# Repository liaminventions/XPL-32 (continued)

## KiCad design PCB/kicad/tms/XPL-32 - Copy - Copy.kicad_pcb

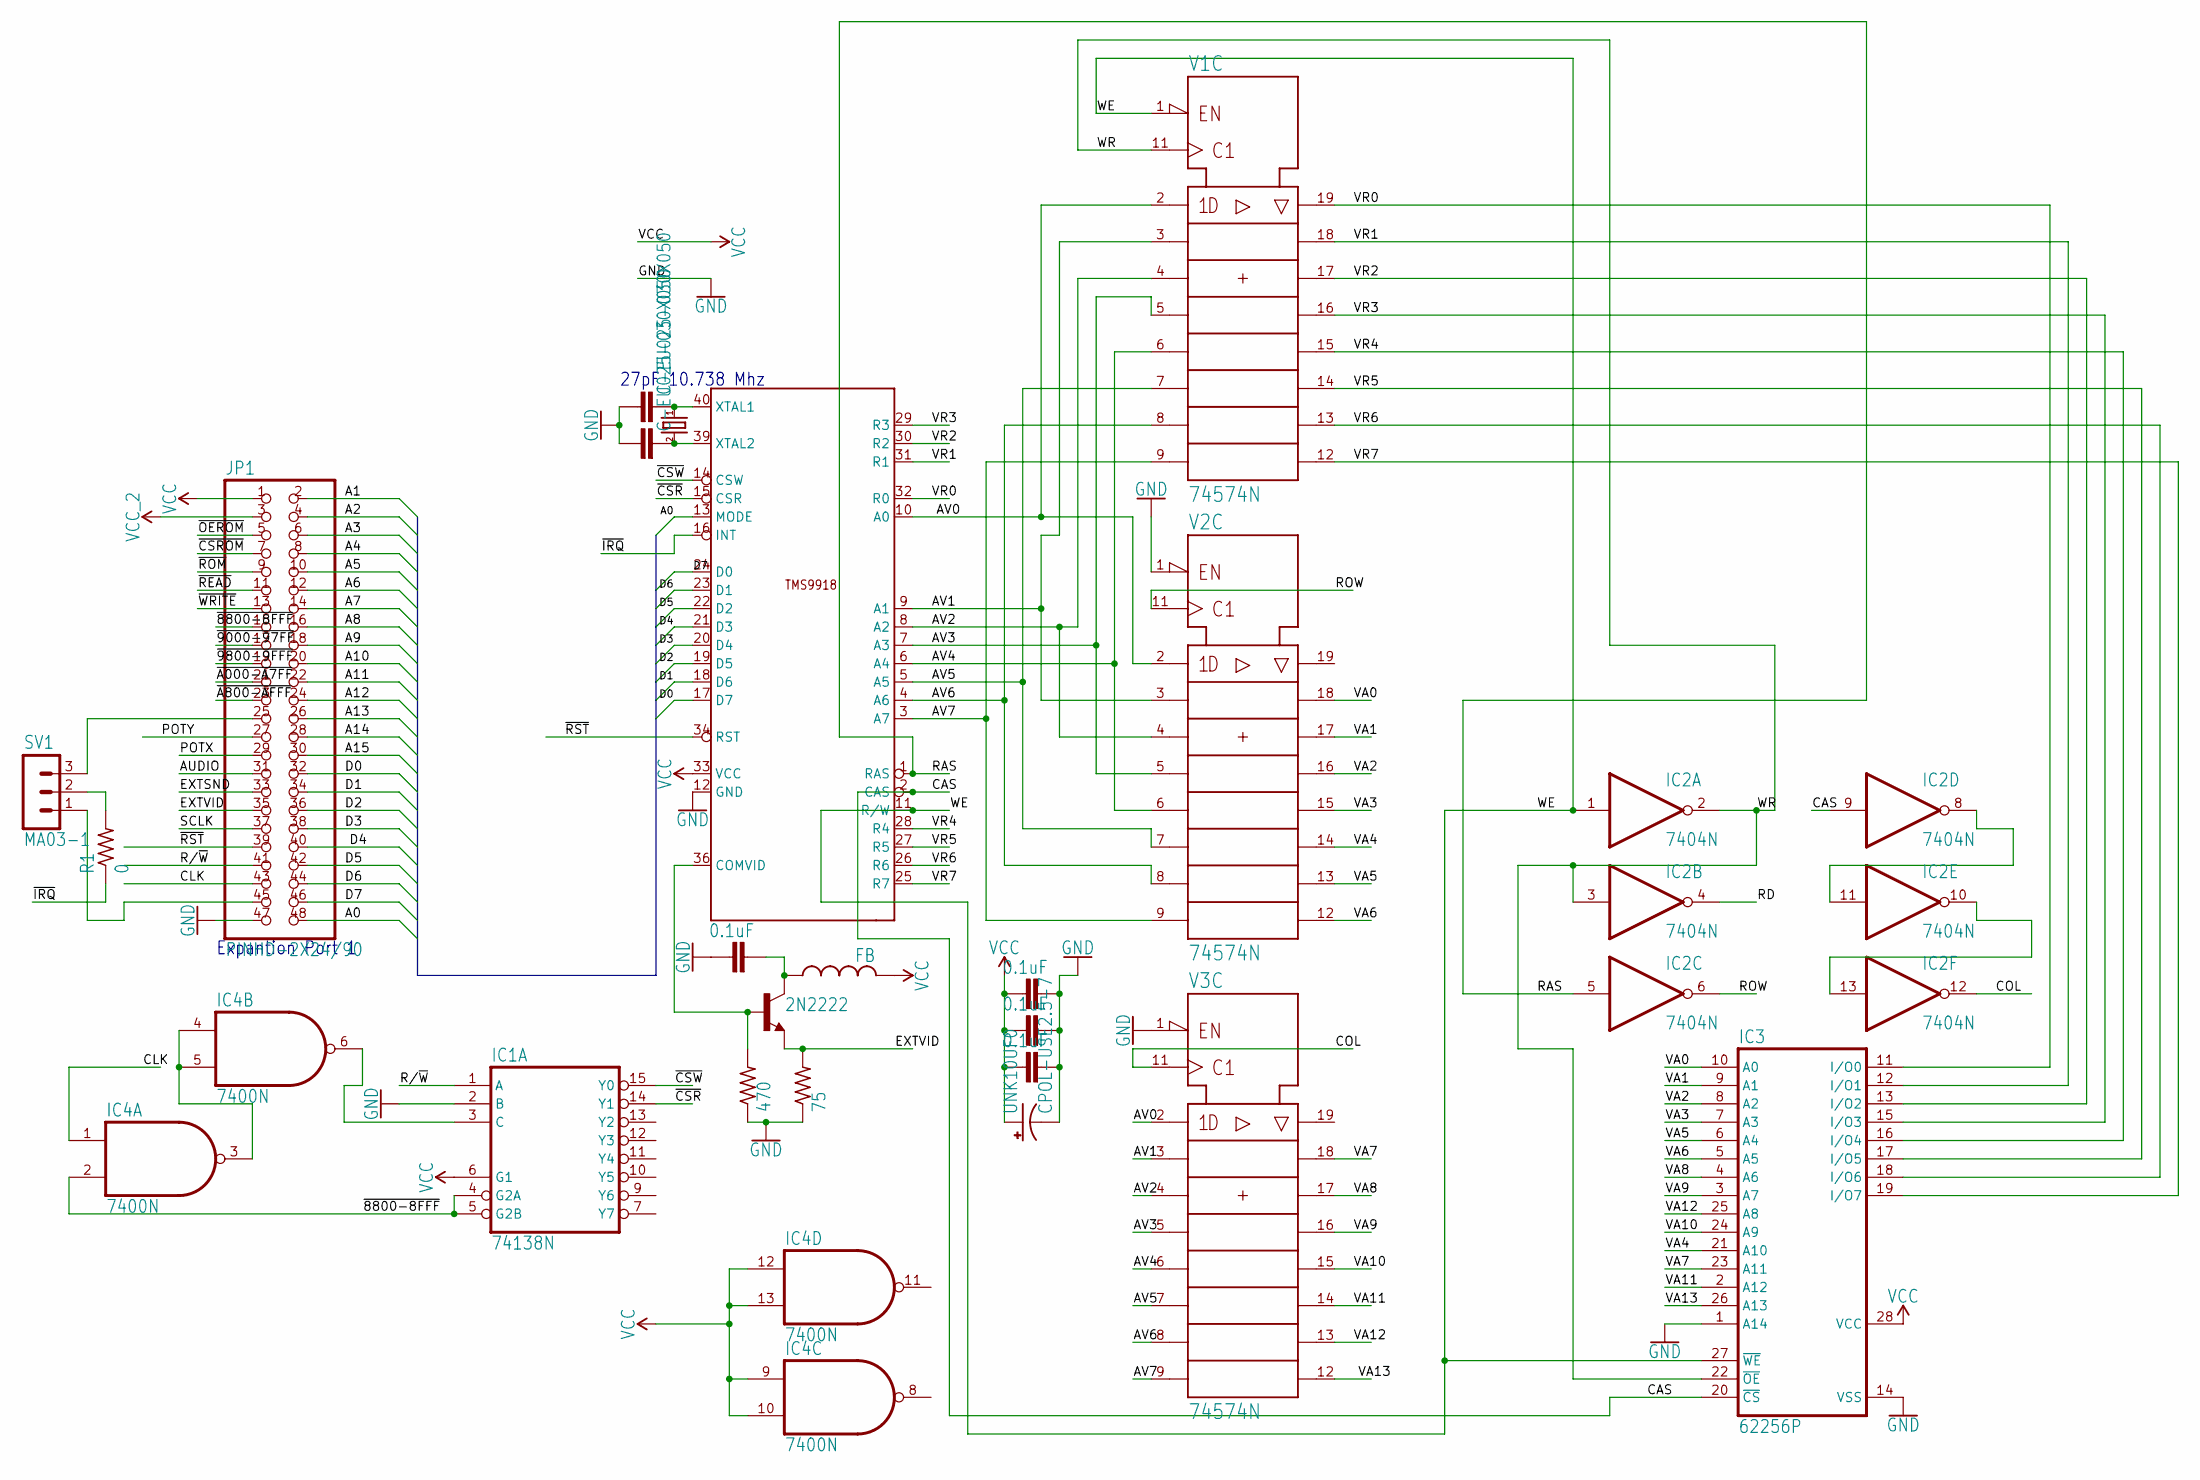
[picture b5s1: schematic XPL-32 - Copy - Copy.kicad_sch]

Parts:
C1, C2, C3, C6: 0.1uF; C025-025X050
IC1: 74138N; DIL16
IC2: 7404N; DIL14
IC3: 62256P; DIL28-6
IC4: 7400N; DIL14
JP1: PINHD-2X24/90; 2X24_90
R1: 0; 0204_7
R9: 470; 0204_7
R10: 75; 0204_7
SV1: MA03-1
T2: 2N2222; TO92-EBC-OVAL
U$4: FB
UNK10.738MHZ0: CRYSTALS-NOGND-HC49; HC49
UNK10UF0: CPOL-USE2.5-7; E2,5-7
UNK30PF0, UNK30PF(2)0: C-EU025-030X050; C025-030X050
V1, V2, V3: 74574N; DIL20
VDP0: TMS9918; DIP-40

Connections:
A0: JP1.48, VDP0.13 (MODE)
A1: JP1.2
A2: JP1.4
A3: JP1.6
A4: JP1.8
A5: JP1.10
A6: JP1.12
A7: JP1.14
A8: JP1.16
A9: JP1.18
A10: JP1.20
A11: JP1.22
A12: JP1.24
A13: JP1.26
A14: JP1.28
A15: JP1.30
AUDIO: JP1.31
AV0: V1.2 (1D), V2.2 (1D), V3.2 (1D), VDP0.10 (A0)
AV1: V1.3 (2D), V2.3 (2D), V3.3 (2D), VDP0.9 (A1)
AV2: V1.4 (3D), V2.4 (3D), V3.4 (3D), VDP0.8 (A2)
AV3: V1.5 (4D), V2.5 (4D), V3.5 (4D), VDP0.7 (A3)
AV4: V1.6 (5D), V2.6 (5D), V3.6 (5D), VDP0.6 (A4)
AV5: V1.7 (6D), V2.7 (6D), V3.7 (6D), VDP0.5 (A5)
AV6: V1.8 (7D), V2.8 (7D), V3.8 (7D), VDP0.4 (A6)
AV7: V1.9 (8D), V2.9 (8D), V3.9 (8D), VDP0.3 (A7)
CAS: IC2.9 (I), IC3.20 (~CS), VDP0.2 (CAS)
CLK: IC4.1 (I0), JP1.43
COL: IC2.12 (O), V3.11 (CLK)
D0: JP1.32, VDP0.17 (D7)
D1: JP1.34, VDP0.18 (D6)
D2: JP1.36, VDP0.19 (D5)
D3: JP1.38, VDP0.20 (D4)
D4: JP1.40, VDP0.21 (D3)
D5: JP1.42, VDP0.22 (D2)
D6: JP1.44, VDP0.23 (D1)
D7: JP1.46, VDP0.24 (D0)
EXTSND: JP1.33
EXTVID: JP1.35, R10.2, T2.E
GND: C1.2, C2.2, C3.2, C6.1, IC1.2 (B), IC1.8 (GND), IC2.7 (GND), IC3.1 (A14), IC3.14 (VSS), IC4.7 (GND), JP1.47, R9.1, R10.1, UNK10UF0.-, UNK30PF0.1, UNK30PF(2)0.1, V1.10 (-UB), V2.1 (~OC), V2.10 (-UB), V3.1 (~OC), V3.10 (-UB), VDP0.12 (GND)
unnamed: IC1.3 (C), IC4.6 (O)
unnamed: JP1.45, SV1.1
unnamed: IC2.8 (O), IC2.11 (I)
unnamed: IC2.10 (O), IC2.13 (I)
unnamed: JP1.25, SV1.3
unnamed: R1.2, SV1.2
unnamed: IC4.3 (O), IC4.4 (I0), IC4.5 (I1)
unnamed: C6.2, T2.C, U$4.P$1 (1)
unnamed: R9.2, T2.B, VDP0.36 (COMVID)
unnamed: UNK10.738MHZ0.1, UNK30PF0.2, VDP0.40 (XTAL1)
unnamed: UNK10.738MHZ0.2, UNK30PF(2)0.2, VDP0.39 (XTAL2)
POTX: JP1.29
POTY: JP1.27
R/~W: IC1.1 (A), JP1.41
RAS: IC2.5 (I), VDP0.1 (RAS)
RD: IC2.4 (O)
ROW: IC2.6 (O), V2.11 (CLK)
SCLK: JP1.37
VA0: IC3.10 (A0), V2.18 (2Q)
VA1: IC3.9 (A1), V2.17 (3Q)
VA2: IC3.8 (A2), V2.16 (4Q)
VA3: IC3.7 (A3), V2.15 (5Q)
VA4: IC3.21 (A10), V2.14 (6Q)
VA5: IC3.6 (A4), V2.13 (7Q)
VA6: IC3.5 (A5), V2.12 (8Q)
VA7: IC3.23 (A11), V3.18 (2Q)
VA8: IC3.4 (A6), V3.17 (3Q)
VA9: IC3.3 (A7), V3.16 (4Q)
VA10: IC3.24 (A9), V3.15 (5Q)
VA11: IC3.2 (A12), V3.14 (6Q)
VA12: IC3.25 (A8), V3.13 (7Q)
VA13: IC3.26 (A13), V3.12 (8Q)
VCC: C1.1, C2.1, C3.1, IC1.6 (G1), IC1.16 (VCC), IC2.14 (VCC), IC3.28 (VCC), IC4.9 (I0), IC4.10 (I1), IC4.12 (I0), IC4.13 (I1), IC4.14 (VCC), JP1.1, U$4.P$2 (2), UNK10UF0.+, V1.20 (+UB), V2.20 (+UB), V3.20 (+UB), VDP0.33 (VCC)
VCC_2: JP1.3
VR0: IC3.11 (I/O0), V1.19 (1Q), VDP0.32 (R0)
VR1: IC3.12 (I/O1), V1.18 (2Q), VDP0.31 (R1)
VR2: IC3.13 (I/O2), V1.17 (3Q), VDP0.30 (R2)
VR3: IC3.15 (I/O3), V1.16 (4Q), VDP0.29 (R3)
VR4: IC3.16 (I/O4), V1.15 (5Q), VDP0.28 (R4)
VR5: IC3.17 (I/O5), V1.14 (6Q), VDP0.27 (R5)
VR6: IC3.18 (I/O6), V1.13 (7Q), VDP0.26 (R6)
VR7: IC3.19 (I/O7), V1.12 (8Q), VDP0.25 (R7)
WE: IC2.1 (I), IC3.27 (~WE), V1.1 (~OC), VDP0.11 (R/W)
WR: IC2.2 (O), IC2.3 (I), IC3.22 (~OE), V1.11 (CLK)
~8800-8FFF: IC1.4 (G2A), IC1.5 (G2B), IC4.2 (I1), JP1.15
~9000-97FF: JP1.17
~9800-9FFF: JP1.19
~A000-A7FF: JP1.21
~A800-AFFF: JP1.23
~CSROM: JP1.7
~CSR: IC1.14 (Y1), VDP0.15 (CSR)
~CSW: IC1.15 (Y0), VDP0.14 (CSW)
~IRQ: R1.1, VDP0.16 (INT)
~OEROM: JP1.5
~READ: JP1.11
~ROM: JP1.9
~RST: JP1.39, VDP0.34 (RST)
~WRITE: JP1.13

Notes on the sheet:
27pF 10.738 Mhz
Expantion Port 1

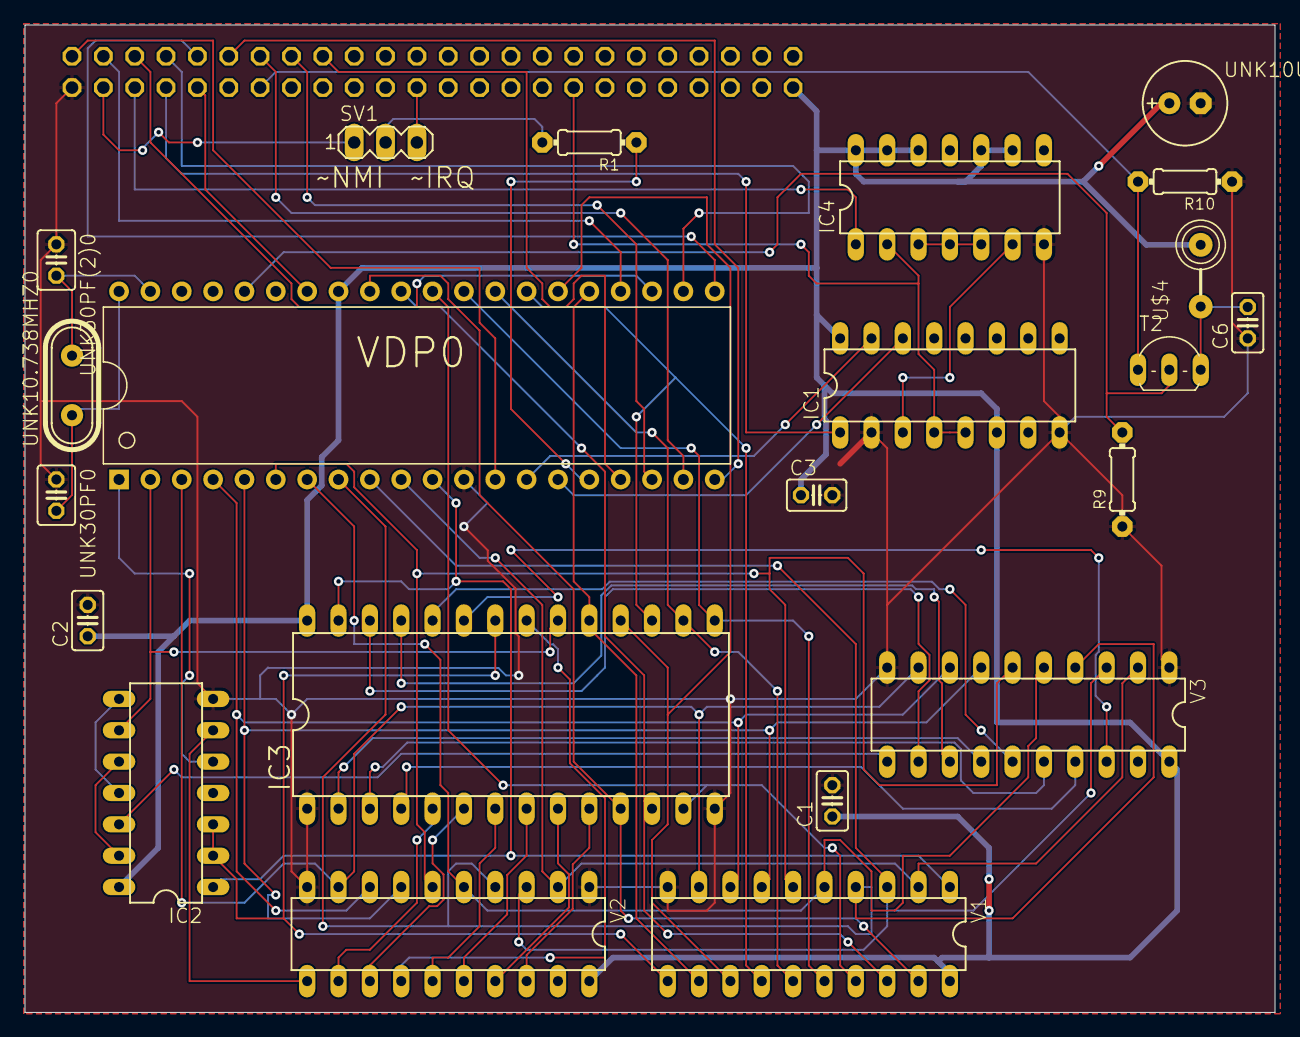
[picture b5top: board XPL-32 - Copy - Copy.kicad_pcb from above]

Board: 2 copper layers, 101.3 x 80.0 mm, 23 parts (1 on the bottom side), 66 nets.

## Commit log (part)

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2023-01-01 have i fixed shortconvert?
2023-01-01 refactor
2023-01-01 maybe its not this?
2023-01-01 oqwe
2023-01-01 With this debug info, i see the issue
2023-01-01 Complete Refactor of the shortconvert system.
2023-01-01 You will work now.
2023-01-01 oh there it is! hehe
2023-01-01 all done!
2023-01-12 clean
2023-01-12 erjieqw
2023-01-12 i dont have time for this
2023-01-20 organise
2023-01-21 add clear command
2023-01-21 fix typos
2023-01-21 add slashpaths?
2023-01-21 fix addr
2023-01-21 wase of time AUUGH
2023-01-23 kernal
2023-01-24 add goofy ahh vim thingy
    aUUUGHHHHH
2023-01-24 update vi
2023-01-24 eqhruewh
2023-01-24 assemble
2023-01-24 iuir
2023-01-24 bugfix
2023-01-24 asmbler da
2023-01-24 Yes.
2023-01-27 update kernal + rearrange + fix memory overlap
2023-01-27 assemble it all together
2023-01-27 update ROM
2023-01-27 werwe
2023-01-31 ok! lets see what arrow keys are
2023-01-31 ccursor test
2023-01-31 generic commit - pay no mind
2023-02-05 add fast mode?
2023-02-05 sizing fix
2023-02-05 quik fixx
2023-02-05 add artifacts
2023-02-05 size
2023-02-05 fix tape kernal defs
2023-02-09 swap
2023-02-21 do not assemble savetest rn
    full re-write of saving
2023-02-21 he he he haw...
    this fixes lots of things...
2023-02-21 noice!
    do not use fat32 in vasm6502 yet
2023-02-21 oh yeah. this is great!
    lots of improvement, but its untested for now
2023-02-21 fix..?
2023-02-22 LETS GO !!
    i think it's done!!!!!!!
    now to test
2023-02-22 test prep (soon)
2023-02-22 testing now
2023-02-22 fix?
2023-02-22 hoho, i got u
2023-02-22 never gonna give you up
2023-02-22 Be fixed now.
2023-02-22 You are done.
2023-02-22 Fired.
2023-02-22 auugh
2023-02-22 gonna try again tomorrow
2023-02-22 oh
    dtrsynhrth
2023-02-22 ho ho ho!
    it works, but its only half a block
2023-02-22 perfect. sd_writesector works
2023-02-22 debuggin time
2023-02-23 many things :100:
    fixin gliches/debug and fix dumb mistakez (lol)
2023-02-23 remove bloat :alien:
2023-02-23 re-arrange and fix savetest i think
2023-02-23 Looking good...
    can't test it now because I didn't bring the XPL with me (on a trip)
2023-02-23 add issue
    overlooked...
2023-02-23 fix EOC handling in fat32_writesector
2023-02-23 workflow: check if cc65 works in a container
2023-02-23 cleanup
2023-02-25 almost there !! (debuggin)
    auugh i mixed up fat32_writenextsector with sd_writesector. probally somewhere else too, hold on...
2023-02-25 ze big e
2023-02-25 oh im dum
    write! not read!
2023-02-25 argh
2023-02-25 Got You.
    "sky sunday" by sinny
2023-02-25 test without
2023-02-25 OMG IT WOKS!
2023-02-25 almost done fixing filesizes
2023-02-25 update bug count
2023-02-25 this is it...
2023-02-25 test
2023-02-25 wow is that what it is?
2023-02-25 ITS DONE!
    oh my...
2023-02-25 IT WORKS! lets try dumping the ROM...
2023-02-25 stability fix?
2023-02-25 AUGH
2023-02-25 FIXED!
    it works!!!!!!!!!!!!!!!!!!!!!!!!!!!!!!!!!!!!!!!!1
2023-02-25 YES! (delete bloat)
2023-02-26 add delete file and set ROM to 16k
2023-02-26 fix
    arrgh inefficient write amount...
2023-02-26 oh i was just dum
2023-02-26 fix aaaaa
    AUUGH !!
2023-02-26 ohhhhhhh
    ic...
2023-02-26 and that
2023-02-26 YAY! RM WORKS!
2023-02-26 add new fat32/sd features to the monitor
2023-02-26 fix assemble
2023-02-26 compile
2023-02-26 :100: EPIC CODER MOMENT !!
2023-02-26 add sd save to the dispatch table
2023-02-26 OMG IT WORKED!
    save command in the monitor! oh wow...
2023-02-26 add file overwriting
2023-02-26 rm that for FAT stability...
2023-02-26 ohhhh
2023-02-26 Be Fixed.
2023-02-26 ohyeah, now RM
2023-02-26 here
2023-02-26 YEAH! RM AND SAVE WORKS!
2023-02-26 check
2023-02-26 All done for today... that was amazing!
2023-02-26 add executable reconition
2023-02-26 KERNAL: update part 1
2023-02-27 finalize kernal def
    done
2023-02-27 add mv and also maybe fix rm? also cleanup
    gotta assemble this on my raspberry pi - hold on...
2023-02-27 whoops - also i gotta add the new fat routines
2023-02-27 ok now i can test
2023-02-27 one moment
2023-02-27 ffind out
2023-02-27 ohhhh is that it?
2023-02-27 fix merge issue
2023-02-27 rguyiwq
2023-02-27 wakeuhyufgef
2023-02-27 Work.
2023-02-27 auugh!!
2023-02-27 oh.
    AUUGH THATS ALL IT IS??!
2023-02-27 -
    -
2023-02-27 Get out, Bug. You are ruining my life.
2023-03-05 redo some things
2023-03-05 quick fix
2023-03-05 ho ho ho!
2023-03-05 fix root name
2023-03-05 why does it display the matrix on startup..?
2023-03-05 fix root symbol
2023-03-05 ehgr
2023-03-06 lesgo
2023-03-06 add dmf
2023-03-06 new image
2023-03-16 fix no directory being showed after root symbol
2023-03-17 iaehh
2023-03-17 changes to asm.sh and rename tms_groove
2023-03-17 oh. (reorginise)
2023-03-17 copy wavrud.s to pong.s (DO NOT USE YET!)
2023-03-18 pong.s better
2023-03-18 fix stuf
2023-03-18 update sd
2023-03-18 ho ho...
2023-03-18 fix ball center
2023-03-18 aeiohr
2023-03-18 oh yeah...
2023-03-18 add vertical dotted line?
2023-03-18 werhnio
2023-03-19 will this fix the paddles?
2023-03-19 waaa
2023-03-19 weiuoo
2023-03-26 clean up
2023-03-27 begin fat32 experiment
2023-03-27 so the journey begins...
2023-03-27 dont run yet
2023-03-27 remove that darn buffer
2023-03-27 rename sectorbounds as updatefat
2023-03-27 begin cluster logic
2023-03-27 augugt
2023-03-27 the big update
2023-03-27 add eoc
2023-03-27 ok! its testing time!
2023-03-28 grr...
2023-03-28 well! atleast thats a step in the right direction!
    more tomorrow...
2023-03-28 hahaha
2023-03-28 when the rts broke the cpu
2023-03-28 will that solve it?
2023-03-28 dumb
2023-03-28 I DID IT!
2023-03-28 good
2023-03-28 IT WORKS!!
    - 512 bytes!
    + fat mirroring!
2023-03-28 add save example
2023-03-28 remove libfat32-stable, as it is no longer stable...
2023-03-28 hoho
2023-03-29 that seemed broken, but i guess it's okay??
2023-03-31 darn
2023-03-31 ..................oh.
2023-04-01 ohh...
2023-04-01 wkhtw
2023-04-01 hehe
2023-04-02 poiuytrew
2023-04-02 oh...
2023-04-02 v bgfvbgtfvrfv
2023-04-02 certified awesome moment (fixed)
2023-04-02 mv is broken - will fix later
2023-04-02 test2
2023-04-02 all fixed!
2023-04-05 tried out decoding a tape file from the XPL!
    it worked!
2023-04-07 add idea
2023-04-09 stuf
2023-04-11 Pong! (big progress)
2023-04-11 grr..
2023-04-11 hotfix
2023-04-11 er...
2023-04-11 hahahhah
2023-04-11 Will it work now?
2023-04-12 test a
2023-04-14 nvim test
2023-04-14 going to add a new licence
2023-04-24 funny fix..?
2023-04-24 the hek was that
2023-04-24 haha yez
2023-05-07 whoops! that was the wrong xa
2023-05-07 fix 2
2023-05-07 ._.
    shoutout to richard stallman-
2023-05-07 the funi
2023-05-13 add modified sdcard_spi sigrok decoder
2023-05-14 oh dang it
2023-05-14 this is where the VSR is irl
2023-05-19 guh?
2023-06-24 clean part 1
2023-06-24 fix gitignore
2023-06-24 fix2
2023-07-06 whoops
2023-07-08 add sd card glitch (idk yet)
2023-07-10 debugging...
2023-07-10 yes, fixed!
2023-07-11 fix shortconvert
2023-07-11 huh?
2023-07-11 is that it?
2023-07-11 ah ok.
2023-07-11 add line ending detection to CAT
2023-07-11 lol i forgot
2023-07-12 huh ok
2023-07-12 why did i do that
2024-10-05 new pcb!!
    this will make it possible to work on the sd card thing yet again!!
2025-06-27 me and xat - WE DID IT.
    sd saving fixed
    i think.
2025-06-27 lemme just put that back lol
2025-06-28 part
2025-06-28 cd fixed, now to restore all other cmds
2025-06-28 change it back!!
    (for now)
2025-06-29 fix error handling
    lol
2025-06-29 ls now uses new path sys
2025-06-30 a bit more fixed ig
